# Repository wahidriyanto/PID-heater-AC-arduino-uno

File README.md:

# PID-Heater AC-RBDdimmer

AC RBDdimmer PID control with tubidity sensor to detect water condition and relay to turn on or off the pump.

*need some more pid tuning

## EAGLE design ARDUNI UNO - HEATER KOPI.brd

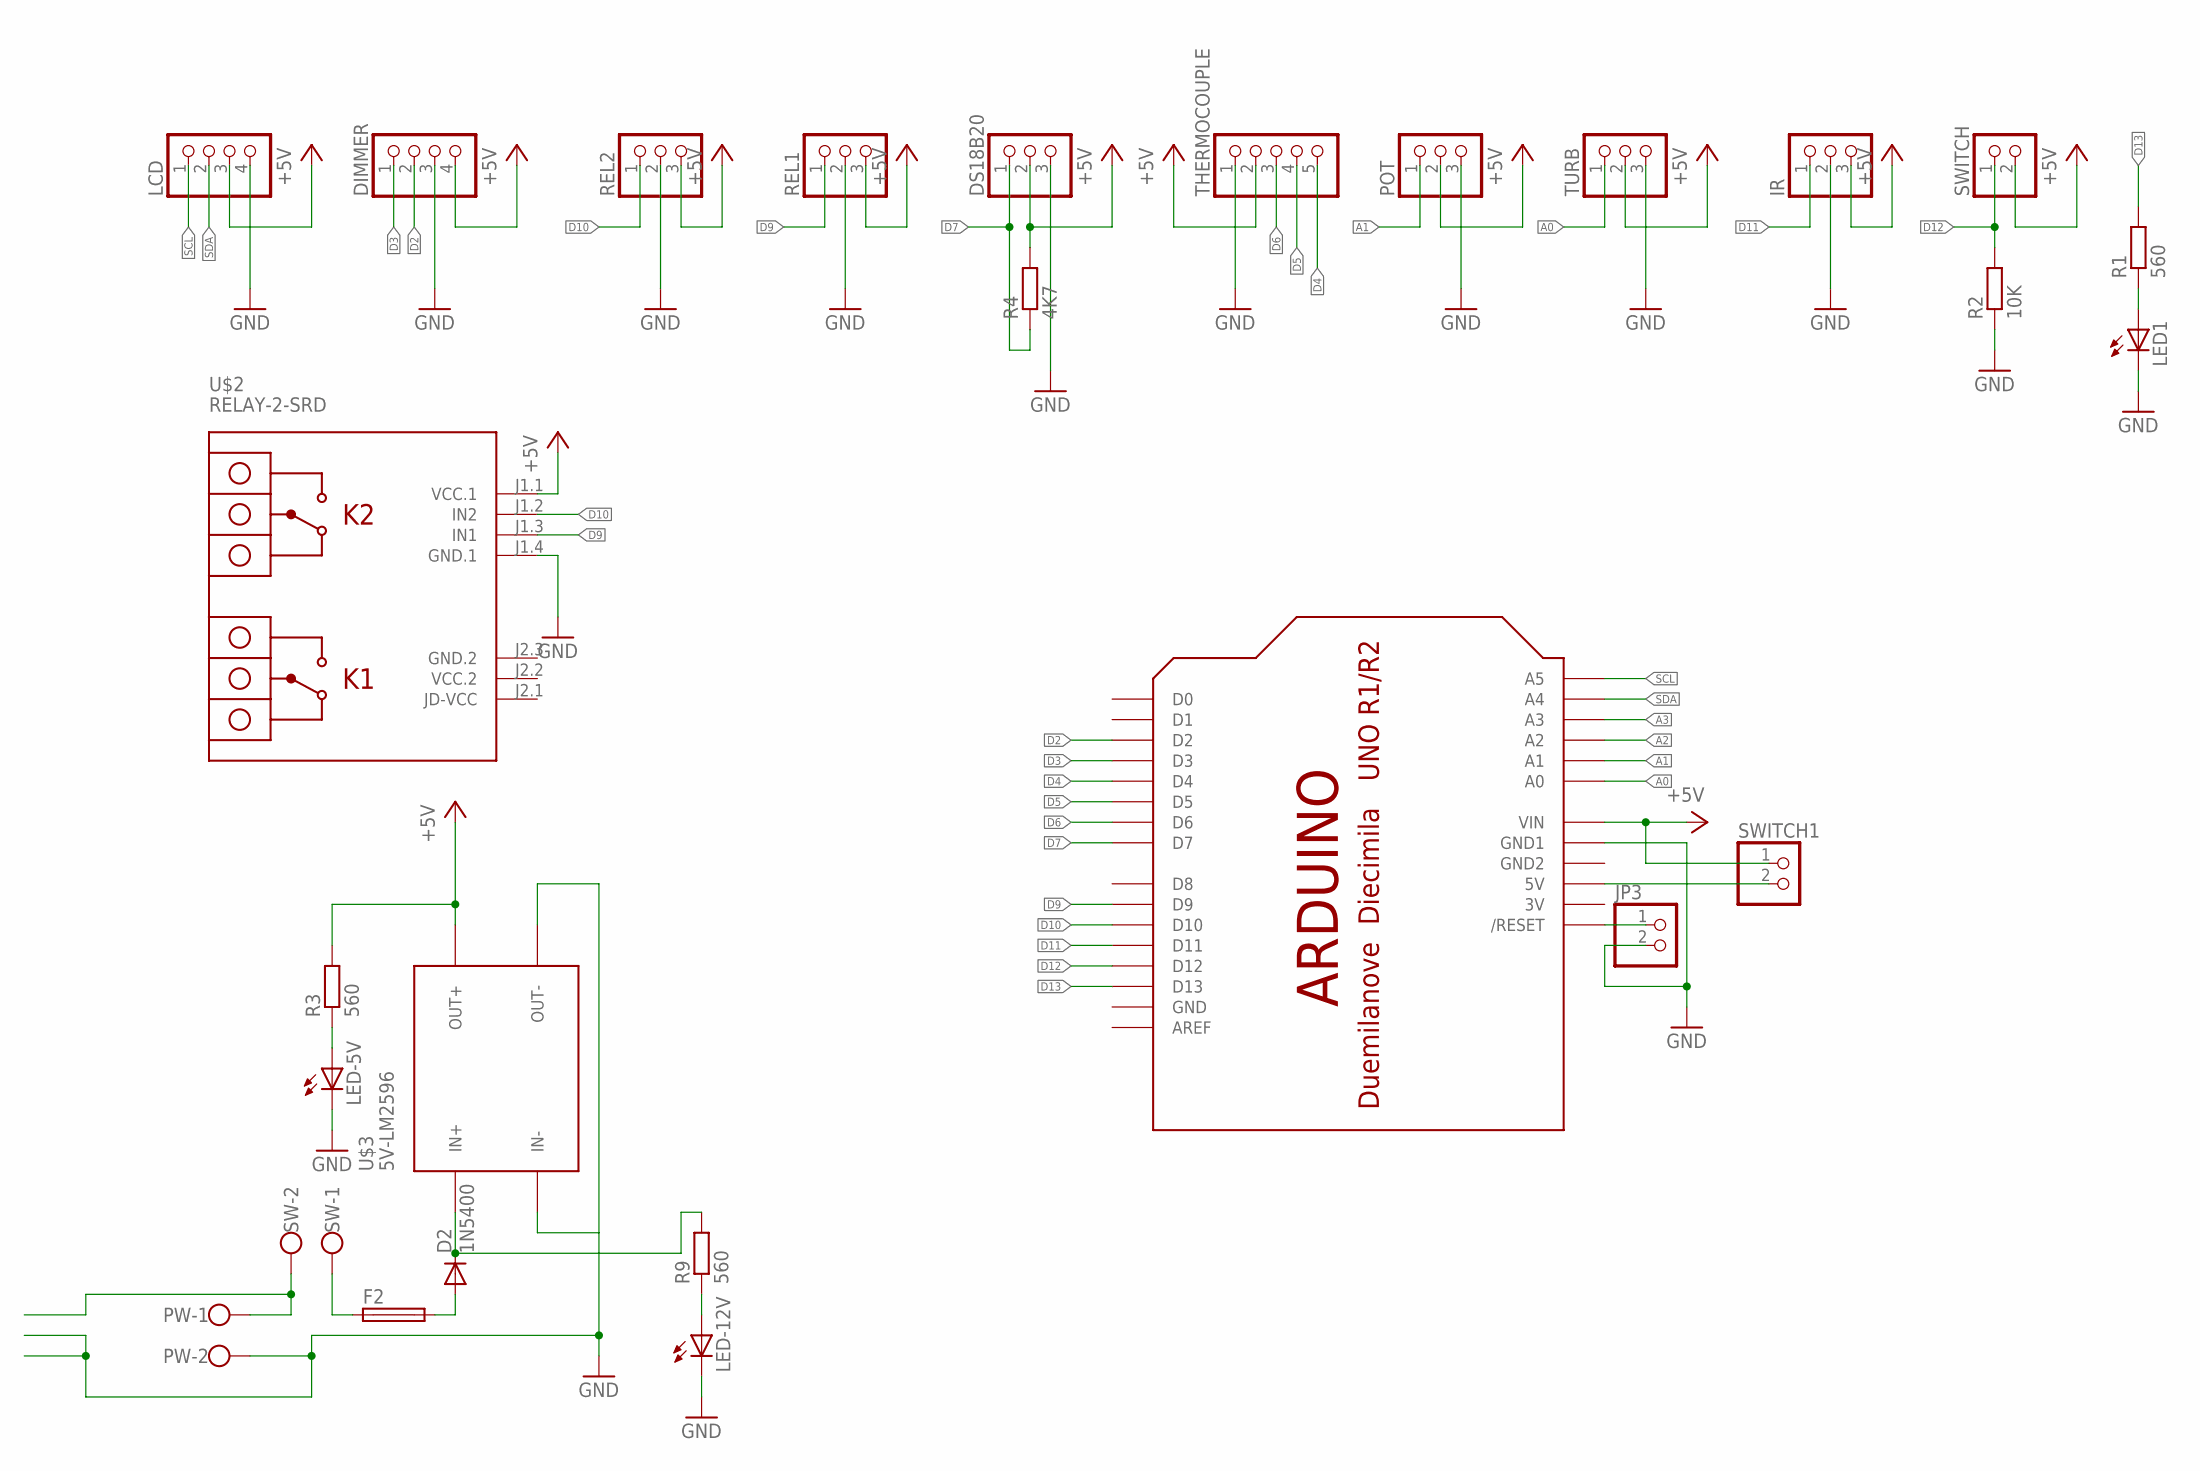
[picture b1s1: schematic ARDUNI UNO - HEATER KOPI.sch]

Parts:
D2: 1N5400; DO201-15
DIMMER: PINHD-1X4; 1X04
DS18B20: PINHD-1X3; 1X03
F2: SH22,5
IR: PINHD-1X3; 1X03
JP3: PINHD-1X2; 1X02
LCD: PINHD-1X4; 1X04
LED1: LED3MM
LED-5V, LED-12V: LED3MM
POT: PINHD-1X3; 1X03
PW: W237-102
R1, R3, R9: 560; 0204/7
R2: 10K; 0204/7
R4: 4K7; 0204/7
REL1, REL2: PINHD-1X3; 1X03
SW: W237-102
SWITCH, SWITCH1: PINHD-1X2; 1X02
THERMOCOUPLE: PINHD-1X5; 1X05
TURB: PINHD-1X3; 1X03
U$1: ARDUINOUNO; ARDUINO
U$2: RELAY-2-SRD
U$3: 5V-LM2596; DC-DC-STEP-DOWN-LM2596

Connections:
3V: U$1.3V
+5V: DIMMER.4, DS18B20.2, IR.3, LCD.3, POT.2, R3.2, R4.2, REL1.3, REL2.3, SWITCH.2, SWITCH1.1, THERMOCOUPLE.2, TURB.2, U$1.VIN, U$2.J1.1 (VCC.1), U$3.OUT+
+12V: D2.C, R9.2, U$3.IN+
A0: TURB.1, U$1.A0
A1: POT.1, U$1.A1
A2: U$1.A2
A3: U$1.A3
D2: DIMMER.2, U$1.D2
D3: DIMMER.1, U$1.D3
D4: THERMOCOUPLE.5, U$1.D4
D5: THERMOCOUPLE.4, U$1.D5
D6: THERMOCOUPLE.3, U$1.D6
D7: DS18B20.1, R4.1, U$1.D7
D9: REL1.1, U$1.D9, U$2.J1.3 (IN1)
D10: REL2.1, U$1.D10, U$2.J1.2 (IN2)
D11: IR.1, U$1.D11
D12: R2.2, SWITCH.1, U$1.D12
D13: R1.2, U$1.D13
GND: DIMMER.3, DS18B20.3, IR.2, JP3.2, LCD.4, LED1.K (C), LED-5V.K (C), LED-12V.K (C), POT.3, PW.2, R2.1, REL1.2, REL2.2, THERMOCOUPLE.1, TURB.3, U$1.GND, U$1.GND1, U$2.J1.4 (GND.1), U$3.IN-, U$3.OUT-
GND2: U$1.GND2
GND.2: U$2.J2.3 (GND.2)
unnamed: F2.1, SW.1
unnamed: JP3.1, U$1.RESET (/RESET)
unnamed: SWITCH1.2, U$1.5V
unnamed: LED1.A, R1.1
unnamed: LED-12V.A, R9.1
unnamed: D2.A, F2.2
unnamed: LED-5V.A, R3.1
unnamed: PW.1, SW.2
SCL: LCD.1, U$1.A5
SDA: LCD.2, U$1.A4
VCC.2: U$2.J2.2 (VCC.2)

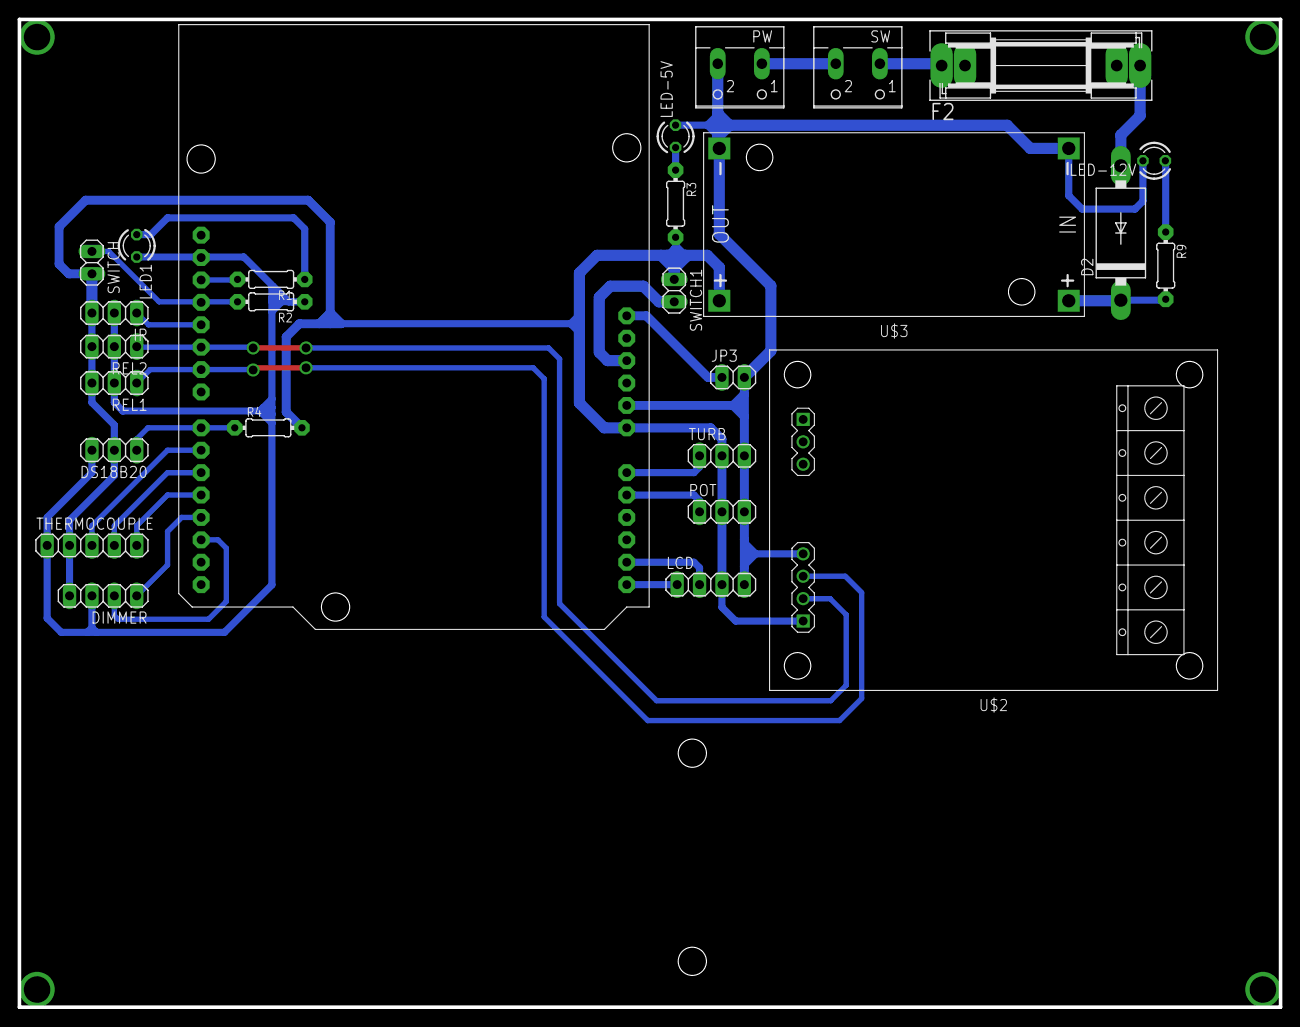
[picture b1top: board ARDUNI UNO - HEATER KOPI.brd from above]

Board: 2 copper layers, 143.0 x 112.0 mm, 27 parts (1 on the bottom side), 26 nets.

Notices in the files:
parts and their libraries:
diy-modules: Released under the Creative Commons Attribution 4.0 International License: http://creativecommons.org/licenses/by/4.0
